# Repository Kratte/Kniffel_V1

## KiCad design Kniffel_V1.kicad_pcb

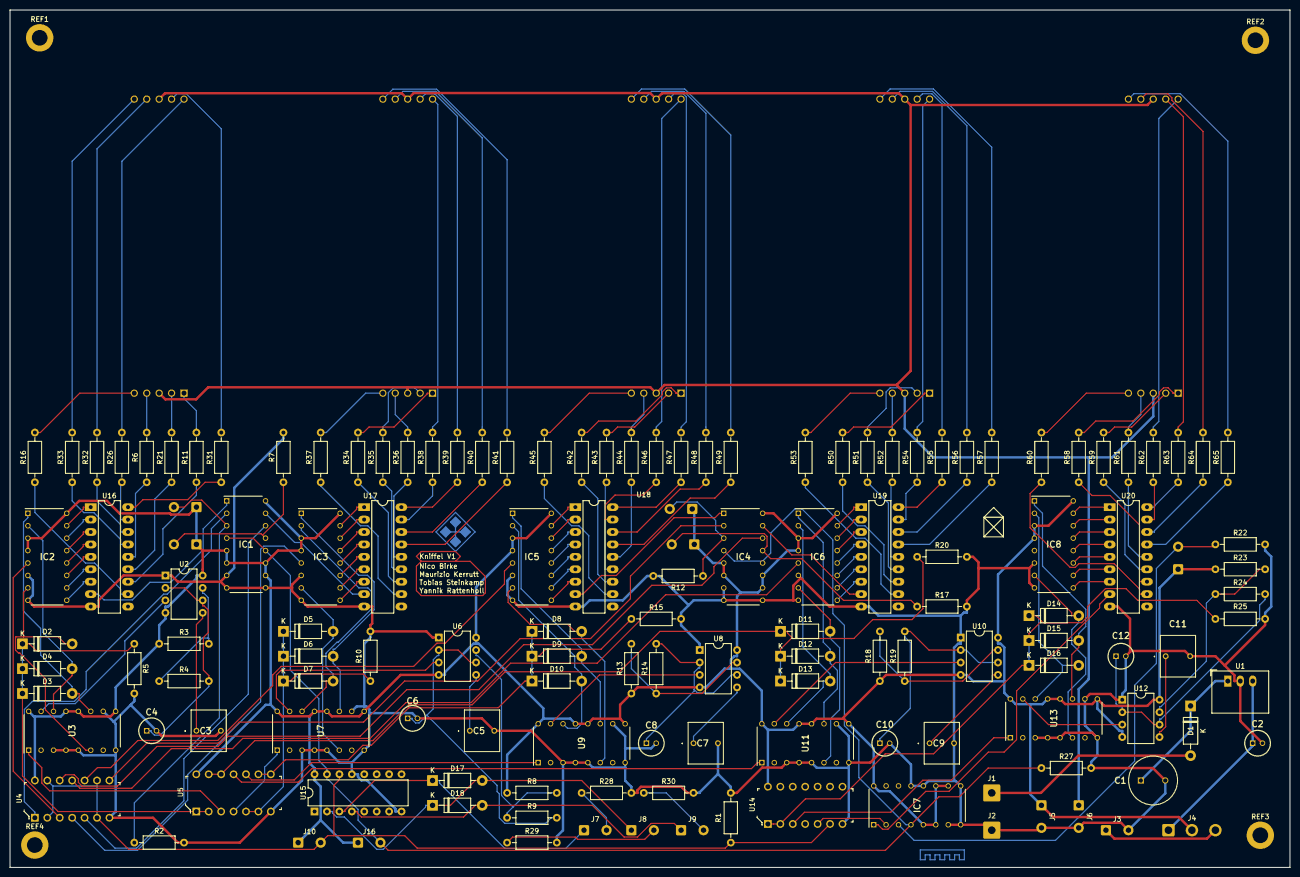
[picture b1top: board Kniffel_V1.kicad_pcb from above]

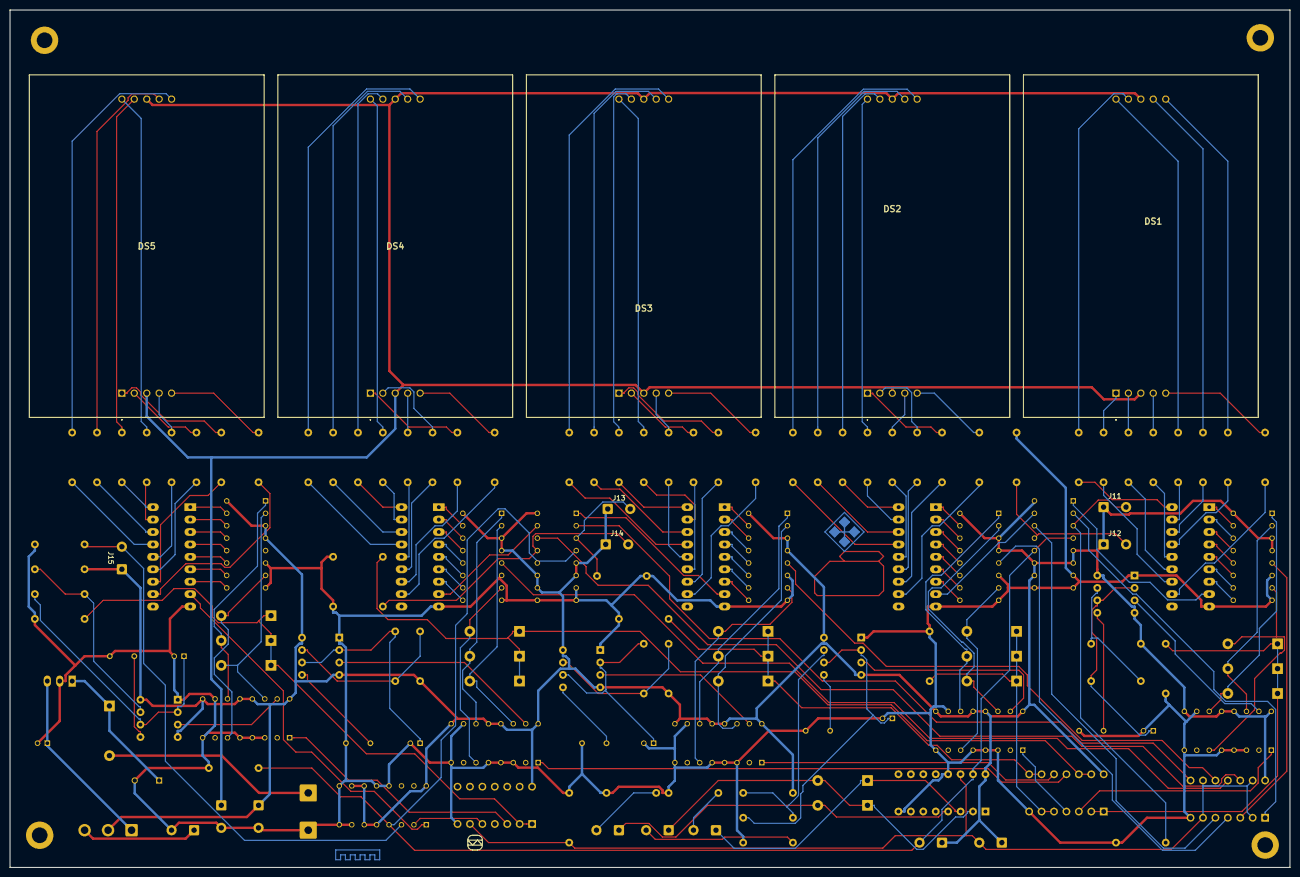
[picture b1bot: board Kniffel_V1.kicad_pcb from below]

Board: 2 copper layers, 261.6 x 175.3 mm, 148 parts (10 on the bottom side), 194 nets.

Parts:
C1: ECA-1HHG331; CAPPRD500W65D1000H1700
C2: ECA-1CM101; CAPPRD200W55D525H1200
C3, C5, C7, C9, C11: FKP2J021001L00HSSD
C4, C6, C8, C10, C12: ECA1HM4R7I; CAPPRD200W55D525H1200
D1: 1N4007; D_DO-41_SOD81_P10.16mm_Horizontal
D2, D3, D4, D5, D6, D7, D8, D9, D10, D11, D12, D13, D14, D15, D16, D17, D18: 1N5817; D_DO-41_SOD81_P10.16mm_Horizontal
DS1, DS2, DS3, DS4, DS5: SA23-12SRWA; SC2312SRWA
IC1, IC4, IC7: CD4027BE; DIP794W53P254L1930H508Q16N
IC2, IC3, IC5, IC6, IC8: CD4511BE; DIP794W53P254L1930H508Q16N
J1: +9V; SolderWire-0.75sqmm_1x01_D1.25mm_OD3.5mm
J2: GND; SolderWire-0.75sqmm_1x01_D1.25mm_OD3.5mm
J3: USB 5V; SolderWire-0.5sqmm_1x02_P4.6mm_D0.9mm_OD2.1mm
J4: Switch; SolderWire-0.75sqmm_1x03_P4.8mm_D1.25mm_OD2.3mm
J5: 5VOUT; SolderWire-0.5sqmm_1x02_P4.6mm_D0.9mm_OD2.1mm
J6: 10VIN; SolderWire-0.5sqmm_1x02_P4.6mm_D0.9mm_OD2.1mm
J7: LED1; SolderWire-0.5sqmm_1x02_P4.6mm_D0.9mm_OD2.1mm
J8: LED2; SolderWire-0.5sqmm_1x02_P4.6mm_D0.9mm_OD2.1mm
J9: LED3; SolderWire-0.5sqmm_1x02_P4.6mm_D0.9mm_OD2.1mm
J10: ROLL_DICE; SolderWire-0.5sqmm_1x02_P4.6mm_D0.9mm_OD2.1mm
J11: DICE1; SolderWire-0.5sqmm_1x02_P4.6mm_D0.9mm_OD2.1mm
J12: DICE2; SolderWire-0.5sqmm_1x02_P4.6mm_D0.9mm_OD2.1mm
J13: DICE3; SolderWire-0.5sqmm_1x02_P4.6mm_D0.9mm_OD2.1mm
J14: DICE4; SolderWire-0.5sqmm_1x02_P4.6mm_D0.9mm_OD2.1mm
J15: DICE5; SolderWire-0.5sqmm_1x02_P4.6mm_D0.9mm_OD2.1mm
J16: RESET; SolderWire-0.5sqmm_1x02_P4.6mm_D0.9mm_OD2.1mm
R1, R27: R3K3; R_Axial_DIN0207_L6.3mm_D2.5mm_P10.16mm_Horizontal
R2, R3, R4, R5, R7, R8, R9, R10, R12, R13, R14, R15, R17, R18, R19, R20, R22, R23, R24, R25: 3K3R; R_Axial_DIN0207_L6.3mm_D2.5mm_P10.16mm_Horizontal
R6, R11, R21, R26, R31, R32, R33, R34, R35, R36, R38, R39, R40, R41, R42, R43, R44, R46, R47, R48, R49, R50, R51, R52, R54, R55, R56, R57, R58, R59, R61, R62, R63, R64, R65: 120R; R_Axial_DIN0207_L6.3mm_D2.5mm_P10.16mm_Horizontal
R16, R37, R45, R53, R60: 270R; R_Axial_DIN0207_L6.3mm_D2.5mm_P10.16mm_Horizontal
R28, R29, R30: 180R; R_Axial_DIN0207_L6.3mm_D2.5mm_P10.16mm_Horizontal
REF1, REF2, REF3, REF4: MountingHole_3.2mm_M3_DIN965_Pad
U1: R-78HB5.0-0.5; Converter_DCDC_RECOM_R-78HB-0.5_THT
U2, U6, U8, U10, U12: NE555P; DIP-8_W7.62mm
U3, U7, U9, U11, U13: CD4029BE; DIP794W53P254L1930H508Q16N
U4, U5, U14: CD4093BE; DIP-14_W3mm
U15: 4017; DIP-16_W7.62mm
U16, U17, U18, U19, U20: ULN2803A; DIP-18_W7.62mm_LongPads

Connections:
+5V: IC1.5 (K2), IC1.6 (J2), IC1.10 (J1), IC1.11 (K1), IC1.16 (VDD), IC2.3 (~LT), IC2.4 (~BL), IC2.16 (VDD), IC3.3 (~LT), IC3.4 (~BL), IC3.16 (VDD), IC4.5 (K2), IC4.6 (J2), IC4.10 (J1), IC4.11 (K1), IC4.16 (VDD), IC5.3 (~LT), IC5.4 (~BL), IC5.16 (VDD), IC6.3 (~LT), IC6.4 (~BL), IC6.16 (VDD), IC7.5 (K2), IC7.6 (J2), IC7.10 (J1), IC7.11 (K1), IC7.16 (VDD), IC8.3 (~LT), IC8.4 (~BL), IC8.16 (VDD), J4.2, J5.1, J10.1, J11.1, J12.1, J13.1, J14.1, J15.1, J16.1, R3.1, R8.1, R13.1, R18.1, R23.1, U2.4 (R), U2.8 (VCC), U3.9 (B/D), U3.12 (J2), U3.13 (J3), U3.16 (VDD), U4.14 (VDD), U5.14 (VDD), U6.4 (R), U6.8 (VCC), U7.9 (B/D), U7.12 (J2), U7.13 (J3), U7.16 (VDD), U8.4 (R), U8.8 (VCC), U9.9 (B/D), U9.12 (J2), U9.13 (J3), U9.16 (VDD), U10.4 (R), U10.8 (VCC), U11.9 (B/D), U11.12 (J2), U11.13 (J3), U11.16 (VDD), U12.4 (R), U12.8 (VCC), U13.9 (B/D), U13.12 (J2), U13.13 (J3), U13.16 (VDD), U14.14 (VDD), U15.16 (VDD)
+10V: DS1.3 (COM_A_1), DS1.8 (COM_A_2), DS2.3 (COM_A_1), DS2.8 (COM_A_2), DS3.3 (COM_A_1), DS3.8 (COM_A_2), DS4.3 (COM_A_1), DS4.8 (COM_A_2), DS5.3 (COM_A_1), DS5.8 (COM_A_2), J6.1
/Dice1/D2: D5.1 (K), D6.1 (K), D7.1 (K), R10.1, U5.5 (C), U5.6 (D)
/Dice1/D2Hold: IC1.14 (~Q1), U4.5 (C)
/Dice1/D2Latch: IC3.5 (LE/~STROBE), U4.4 (K)
/Dice1/D2Q: IC1.15 (Q1), U17.8 (I8)
/Dice1/D2R: U5.4 (K), U7.1 (PE)
/Dice1/D2Set: IC1.13 (CLOCK1), J12.2, R7.1
/Dice1/D3: D8.1 (K), D9.1 (K), D10.1 (K), R15.1, U5.8 (E), U5.9 (F)
/Dice1/D3Hold: IC4.2 (~Q2), U4.8 (E)
/Dice1/D3Latch: IC5.5 (LE/~STROBE), U4.10 (L)
/Dice1/D3R: U5.10 (L), U9.1 (PE)
/Dice1/D4: D11.1 (K), D12.1 (K), D13.1 (K), R20.1, U5.12 (G), U5.13 (H)
/Dice1/D4Hold: IC4.14 (~Q1), U4.12 (G)
/Dice1/D4Latch: IC6.5 (LE/~STROBE), U4.11 (M)
/Dice1/D4R: U5.11 (M), U11.1 (PE)
/Dice1/Roll: J10.2, R1.1, U4.2 (B), U4.6 (D), U4.9 (F), U4.13 (H), U14.6 (D), U15.14 (CLK)
/Dice3/D4Q: IC4.15 (Q1), U19.8 (I8)
/Dice3/D4Set: IC4.13 (CLOCK1), J14.2, R17.1
D5Hold: IC7.2 (~Q2), U14.5 (C)
GND: C1.2, C2.2, C3.2, C4.2, C5.2, C6.2, C7.2, C8.2, C9.2, C10.2, C11.2, C12.2, IC1.7 (SET2), IC1.8 (VSS), IC1.9 (SET1), IC2.6 (D_1), IC2.8 (VSS), IC3.6 (D_1), IC3.8 (VSS), IC4.7 (SET2), IC4.8 (VSS), IC4.9 (SET1), IC5.6 (D_1), IC5.8 (VSS), IC6.6 (D_1), IC6.8 (VSS), IC7.7 (SET2), IC7.8 (VSS), IC7.9 (SET1), IC7.12 (RESET1), IC7.13 (CLOCK1), IC8.6 (D_1), IC8.8 (VSS), J2.1, J3.2, J5.2, J6.2, R1.2, R2.2, R5.2, R7.2, R10.2, R12.2, R15.2, R17.2, R20.2, R22.2, R25.2, R27.2, R28.2, R29.2, R30.2, U1.2 (GND), U2.1 (GND), U3.3 (J4), U3.4 (J1), U3.5 (Cin), U3.8 (VSS), U3.10 (U/D), U4.7 (VCC), U5.7 (VCC), U6.1 (GND), U7.3 (J4), U7.4 (J1), U7.5 (Cin), U7.8 (VSS), U7.10 (U/D), U8.1 (GND), U9.3 (J4), U9.4 (J1), U9.5 (Cin), U9.8 (VSS), U9.10 (U/D), U10.1 (GND), U11.3 (J4), U11.4 (J1), U11.5 (Cin), U11.8 (VSS), U11.10 (U/D), U12.1 (GND), U13.3 (J4), U13.4 (J1), U13.5 (Cin), U13.8 (VSS), U13.10 (U/D), U14.7 (VCC), U15.8 (VSS), U15.13 (CKEN), U16.9 (GND), U17.9 (GND), U18.9 (GND), U19.9 (GND), U20.9 (GND)
unnamed: C1.1, D1.1 (K), U1.1 (IN)
unnamed: C2.1, J4.1, U1.3 (OUT)
unnamed: C3.1, U2.5 (CV)
unnamed: C4.1, R4.2, U2.2 (TR), U2.6 (THR)
unnamed: C5.1, U6.5 (CV)
unnamed: C6.1, R9.2, U6.2 (TR), U6.6 (THR)
unnamed: C7.1, U8.5 (CV)
unnamed: C8.1, R14.2, U8.2 (TR), U8.6 (THR)
unnamed: C9.1, U10.5 (CV)
unnamed: C10.1, R19.2, U10.2 (TR), U10.6 (THR)
unnamed: C11.1, U12.5 (CV)
unnamed: C12.1, R24.2, U12.2 (TR), U12.6 (THR)
unnamed: D1.2 (A), J1.1
unnamed: D2.1 (K), D3.1 (K), D4.1 (K), R5.1, U5.1 (A), U5.2 (B)
unnamed: D2.2 (A), IC2.7 (A_1), U3.6 (Q1)
unnamed: D3.2 (A), IC2.1 (B_1), U3.11 (Q2)
unnamed: D4.2 (A), IC2.2 (C_1), U3.14 (Q3)
unnamed: D5.2 (A), IC3.7 (A_1), U7.6 (Q1)
unnamed: D6.2 (A), IC3.1 (B_1), U7.11 (Q2)
unnamed: D7.2 (A), IC3.2 (C_1), U7.14 (Q3)
unnamed: D8.2 (A), IC5.7 (A_1), U9.6 (Q1)
unnamed: D9.2 (A), IC5.1 (B_1), U9.11 (Q2)
unnamed: D10.2 (A), IC5.2 (C_1), U9.14 (Q3)
unnamed: D11.2 (A), IC6.7 (A_1), U11.6 (Q1)
unnamed: D12.2 (A), IC6.1 (B_1), U11.11 (Q2)
unnamed: D13.2 (A), IC6.2 (C_1), U11.14 (Q3)
unnamed: D14.1 (K), D15.1 (K), D16.1 (K), R25.1, U14.1 (A), U14.2 (B)
unnamed: D14.2 (A), IC8.7 (A_1), U13.6 (Q1)
unnamed: D15.2 (A), IC8.1 (B_1), U13.11 (Q2)
unnamed: D16.2 (A), IC8.2 (C_1), U13.14 (Q3)
unnamed: D17.1 (K), J7.1, U15.3 (Q0)
unnamed: D17.2 (A), D18.1 (K), J8.1, U15.2 (Q1)
unnamed: D18.2 (A), J9.1, U15.4 (Q2)
unnamed: DS1.1 (K_E), R11.2
unnamed: DS1.2 (K_D), R21.2
unnamed: DS1.4 (K_C), R6.2
unnamed: DS1.5 (K_DP), R16.2
unnamed: DS1.6 (K_B), R33.2
unnamed: DS1.7 (K_A), R32.2
unnamed: DS1.9 (K_F), R31.2
unnamed: DS1.10 (K_G), R26.2
unnamed: DS2.1 (K_E), R34.2
unnamed: DS2.2 (K_D), R35.2
unnamed: DS2.4 (K_C), R36.2
unnamed: DS2.5 (K_DP), R37.2
unnamed: DS2.6 (K_B), R41.2
unnamed: DS2.7 (K_A), R40.2
unnamed: DS2.9 (K_F), R39.2
unnamed: DS2.10 (K_G), R38.2
unnamed: DS3.1 (K_E), R42.2
unnamed: DS3.2 (K_D), R43.2
unnamed: DS3.4 (K_C), R44.2
unnamed: DS3.5 (K_DP), R45.2
unnamed: DS3.6 (K_B), R49.2
unnamed: DS3.7 (K_A), R48.2
unnamed: DS3.9 (K_F), R47.2
unnamed: DS3.10 (K_G), R46.2
unnamed: DS4.1 (K_E), R50.2
unnamed: DS4.2 (K_D), R51.2
unnamed: DS4.4 (K_C), R52.2
unnamed: DS4.5 (K_DP), R53.2
unnamed: DS4.6 (K_B), R57.2
unnamed: DS4.7 (K_A), R56.2
unnamed: DS4.9 (K_F), R55.2
unnamed: DS4.10 (K_G), R54.2
unnamed: DS5.1 (K_E), R58.2
unnamed: DS5.2 (K_D), R59.2
unnamed: DS5.4 (K_C), R61.2
unnamed: DS5.5 (K_DP), R60.2
unnamed: DS5.6 (K_B), R65.2
unnamed: DS5.7 (K_A), R64.2
unnamed: DS5.9 (K_F), R63.2
unnamed: DS5.10 (K_G), R62.2
unnamed: IC1.1 (Q2), U16.8 (I8)
unnamed: IC1.2 (~Q2), U4.1 (A)
unnamed: IC1.3 (CLOCK2), J11.2, R2.1
unnamed: IC2.5 (LE/~STROBE), U4.3 (J)
unnamed: IC2.9 (E), U16.7 (I7)
unnamed: IC2.10 (D_2), U16.6 (I6)
unnamed: IC2.11 (C_2), U16.5 (I5)
unnamed: IC2.12 (B_2), U16.4 (I4)
unnamed: IC2.13 (A_2), U16.3 (I3)
unnamed: IC2.14 (G), U16.2 (I2)
unnamed: IC2.15 (F), U16.1 (I1)
unnamed: IC3.9 (E), U17.7 (I7)
unnamed: IC3.10 (D_2), U17.6 (I6)
unnamed: IC3.11 (C_2), U17.5 (I5)
unnamed: IC3.12 (B_2), U17.4 (I4)
unnamed: IC3.13 (A_2), U17.3 (I3)
unnamed: IC3.14 (G), U17.2 (I2)
unnamed: IC3.15 (F), U17.1 (I1)
unnamed: IC4.1 (Q2), U18.8 (I8)
unnamed: IC4.3 (CLOCK2), J13.2, R12.1
unnamed: IC5.9 (E), U18.7 (I7)
unnamed: IC5.10 (D_2), U18.6 (I6)
unnamed: IC5.11 (C_2), U18.5 (I5)
unnamed: IC5.12 (B_2), U18.4 (I4)
unnamed: IC5.13 (A_2), U18.3 (I3)
unnamed: IC5.14 (G), U18.2 (I2)
unnamed: IC5.15 (F), U18.1 (I1)
unnamed: IC6.9 (E), U19.7 (I7)
unnamed: IC6.10 (D_2), U19.6 (I6)
unnamed: IC6.11 (C_2), U19.5 (I5)
unnamed: IC6.12 (B_2), U19.4 (I4)
unnamed: IC6.13 (A_2), U19.3 (I3)
unnamed: IC6.14 (G), U19.2 (I2)
unnamed: IC6.15 (F), U19.1 (I1)
unnamed: IC7.1 (Q2), U20.8 (I8)
unnamed: IC7.3 (CLOCK2), J15.2, R22.1
unnamed: IC8.9 (E), U20.7 (I7)
unnamed: IC8.10 (D_2), U20.6 (I6)
unnamed: IC8.11 (C_2), U20.5 (I5)
unnamed: IC8.12 (B_2), U20.4 (I4)
unnamed: IC8.13 (A_2), U20.3 (I3)
unnamed: IC8.14 (G), U20.2 (I2)
unnamed: IC8.15 (F), U20.1 (I1)
unnamed: J3.1, J4.3
unnamed: J7.2, R28.1
unnamed: J8.2, R29.1
unnamed: J9.2, R30.1
unnamed: R3.2, R4.1, U2.7 (DIS)
unnamed: R6.1, U16.14 (O5)
unnamed: R8.2, R9.1, U6.7 (DIS)
unnamed: R11.1, U16.12 (O7)
unnamed: R13.2, R14.1, U8.7 (DIS)
unnamed: R16.1, U16.11 (O8)
unnamed: R18.2, R19.1, U10.7 (DIS)
unnamed: R21.1, U16.13 (O6)
unnamed: R23.2, R24.1, U12.7 (DIS)
unnamed: R26.1, U16.17 (O2)
unnamed: R31.1, U16.18 (O1)
unnamed: R32.1, U16.16 (O3)
unnamed: R33.1, U16.15 (O4)
unnamed: R34.1, U17.12 (O7)
unnamed: R35.1, U17.13 (O6)
unnamed: R36.1, U17.14 (O5)
unnamed: R37.1, U17.11 (O8)
unnamed: R38.1, U17.17 (O2)
unnamed: R39.1, U17.18 (O1)
unnamed: R40.1, U17.16 (O3)
unnamed: R41.1, U17.15 (O4)
unnamed: R42.1, U18.12 (O7)
unnamed: R43.1, U18.13 (O6)
unnamed: R44.1, U18.14 (O5)
unnamed: R45.1, U18.11 (O8)
unnamed: R46.1, U18.17 (O2)
unnamed: R47.1, U18.18 (O1)
unnamed: R48.1, U18.16 (O3)
unnamed: R49.1, U18.15 (O4)
unnamed: R50.1, U19.12 (O7)
unnamed: R51.1, U19.13 (O6)
unnamed: R52.1, U19.14 (O5)
unnamed: R53.1, U19.11 (O8)
unnamed: R54.1, U19.17 (O2)
unnamed: R55.1, U19.18 (O1)
unnamed: R56.1, U19.16 (O3)
unnamed: R57.1, U19.15 (O4)
unnamed: R58.1, U20.12 (O7)
unnamed: R59.1, U20.13 (O6)
unnamed: R60.1, U20.11 (O8)
unnamed: R61.1, U20.14 (O5)
unnamed: R62.1, U20.17 (O2)
unnamed: R63.1, U20.18 (O1)
unnamed: R64.1, U20.16 (O3)
unnamed: R65.1, U20.15 (O4)
unnamed: U2.3 (Q), U3.15 (CK)
unnamed: U3.1 (PE), U5.3 (J)
unnamed: U6.3 (Q), U7.15 (CK)
unnamed: U8.3 (Q), U9.15 (CK)
unnamed: U10.3 (Q), U11.15 (CK)
unnamed: U12.3 (Q), U13.15 (CK)
unnamed: U13.1 (PE), U14.3 (J)
Reset: IC1.4 (RESET2), IC1.12 (RESET1), IC4.4 (RESET2), IC4.12 (RESET1), IC7.4 (RESET2), J16.2, R27.1, U15.15 (Reset)

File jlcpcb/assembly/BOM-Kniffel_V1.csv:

Comment,Designator,Footprint,LCSC
+9V,J1,SolderWire-0.75sqmm_1x01_D1.25mm_OD3.5mm,
3K3R,R18,R_Axial_DIN0207_L6.3mm_D2.5mm_P10.16mm_Horizontal,
CD4511BE,IC3,DIP794W53P254L1930H508Q16N,
3K3R,R10,R_Axial_DIN0207_L6.3mm_D2.5mm_P10.16mm_Horizontal,
3K3R,R25,R_Axial_DIN0207_L6.3mm_D2.5mm_P10.16mm_Horizontal,
3K3R,R4,R_Axial_DIN0207_L6.3mm_D2.5mm_P10.16mm_Horizontal,
3K3R,R15,R_Axial_DIN0207_L6.3mm_D2.5mm_P10.16mm_Horizontal,
3K3R,R20,R_Axial_DIN0207_L6.3mm_D2.5mm_P10.16mm_Horizontal,
3K3R,R3,R_Axial_DIN0207_L6.3mm_D2.5mm_P10.16mm_Horizontal,
CD4511BE,IC5,DIP794W53P254L1930H508Q16N,
NE555P,U6,DIP-8_W7.62mm,
FKP2J021001L00HSSD,C3,FKP2J021001L00HSSD,
3K3R,R2,R_Axial_DIN0207_L6.3mm_D2.5mm_P10.16mm_Horizontal,
1N5817,D11,D_DO-41_SOD81_P10.16mm_Horizontal,
CD4511BE,IC8,DIP794W53P254L1930H508Q16N,
1N4007,D1,D_DO-41_SOD81_P10.16mm_Horizontal,
CD4511BE,IC2,DIP794W53P254L1930H508Q16N,
1N5817,D3,D_DO-41_SOD81_P10.16mm_Horizontal,
NE555P,U10,DIP-8_W7.62mm,
Switch,J4,SolderWire-0.75sqmm_1x03_P4.8mm_D1.25mm_OD2.3mm,
FKP2J021001L00HSSD,C11,FKP2J021001L00HSSD,
1N5817,D10,D_DO-41_SOD81_P10.16mm_Horizontal,
CD4029BE,U7,DIP794W53P254L1930H508Q16N,
1N5817,D7,D_DO-41_SOD81_P10.16mm_Horizontal,
CD4027BE,IC4,DIP794W53P254L1930H508Q16N,
270R,R16,R_Axial_DIN0207_L6.3mm_D2.5mm_P10.16mm_Horizontal,
1N5817,D16,D_DO-41_SOD81_P10.16mm_Horizontal,
GND,J2,SolderWire-0.75sqmm_1x01_D1.25mm_OD3.5mm,
ECA-1CM101,C2,CAPPRD200W55D525H1200,
ECA1HM4R7I,C4,CAPPRD200W55D525H1200,
CD4093BE,U4,DIP-14_W3mm,
1N5817,D8,D_DO-41_SOD81_P10.16mm_Horizontal,
3K3R,R9,R_Axial_DIN0207_L6.3mm_D2.5mm_P10.16mm_Horizontal,
1N5817,D6,D_DO-41_SOD81_P10.16mm_Horizontal,
3K3R,R22,R_Axial_DIN0207_L6.3mm_D2.5mm_P10.16mm_Horizontal,
1N5817,D13,D_DO-41_SOD81_P10.16mm_Horizontal,
NE555P,U2,DIP-8_W7.62mm,
1N5817,D4,D_DO-41_SOD81_P10.16mm_Horizontal,
CD4029BE,U3,DIP794W53P254L1930H508Q16N,
3K3R,R8,R_Axial_DIN0207_L6.3mm_D2.5mm_P10.16mm_Horizontal,
ECA1HM4R7I,C10,CAPPRD200W55D525H1200,
120R,R26,R_Axial_DIN0207_L6.3mm_D2.5mm_P10.16mm_Horizontal,
ECA1HM4R7I,C12,CAPPRD200W55D525H1200,
3K3R,R12,R_Axial_DIN0207_L6.3mm_D2.5mm_P10.16mm_Horizontal,
3K3R,R7,R_Axial_DIN0207_L6.3mm_D2.5mm_P10.16mm_Horizontal,
R3K3,R1,R_Axial_DIN0207_L6.3mm_D2.5mm_P10.16mm_Horizontal,
CD4029BE,U11,DIP794W53P254L1930H508Q16N,
CD4027BE,IC7,DIP794W53P254L1930H508Q16N,
R-78HB5.0-0.5,U1,Converter_DCDC_RECOM_R-78HB-0.5_THT,
1N5817,D15,D_DO-41_SOD81_P10.16mm_Horizontal,
USB 5V,J3,SolderWire-0.5sqmm_1x02_P4.6mm_D0.9mm_OD2.1mm,
CD4511BE,IC6,DIP794W53P254L1930H508Q16N,
NE555P,U12,DIP-8_W7.62mm,
CD4093BE,U5,DIP-14_W3mm,
FKP2J021001L00HSSD,C5,FKP2J021001L00HSSD,
1N5817,D2,D_DO-41_SOD81_P10.16mm_Horizontal,
3K3R,R5,R_Axial_DIN0207_L6.3mm_D2.5mm_P10.16mm_Horizontal,
FKP2J021001L00HSSD,C7,FKP2J021001L00HSSD,
3K3R,R24,R_Axial_DIN0207_L6.3mm_D2.5mm_P10.16mm_Horizontal,
ECA1HM4R7I,C8,CAPPRD200W55D525H1200,
1N5817,D14,D_DO-41_SOD81_P10.16mm_Horizontal,
CD4093BE,U14,DIP-14_W3mm,
CD4027BE,IC1,DIP794W53P254L1930H508Q16N,
3K3R,R23,R_Axial_DIN0207_L6.3mm_D2.5mm_P10.16mm_Horizontal,
ECA1HM4R7I,C6,CAPPRD200W55D525H1200,
1N5817,D5,D_DO-41_SOD81_P10.16mm_Horizontal,
120R,R6,R_Axial_DIN0207_L6.3mm_D2.5mm_P10.16mm_Horizontal,
3K3R,R17,R_Axial_DIN0207_L6.3mm_D2.5mm_P10.16mm_Horizontal,
120R,R21,R_Axial_DIN0207_L6.3mm_D2.5mm_P10.16mm_Horizontal,
1N5817,D12,D_DO-41_SOD81_P10.16mm_Horizontal,
ECA-1HHG331,C1,CAPPRD500W65D1000H1700,
120R,R11,R_Axial_DIN0207_L6.3mm_D2.5mm_P10.16mm_Horizontal,
FKP2J021001L00HSSD,C9,FKP2J021001L00HSSD,
3K3R,R13,R_Axial_DIN0207_L6.3mm_D2.5mm_P10.16mm_Horizontal,
3K3R,R19,R_Axial_DIN0207_L6.3mm_D2.5mm_P10.16mm_Horizontal,
3K3R,R14,R_Axial_DIN0207_L6.3mm_D2.5mm_P10.16mm_Horizontal,
1N5817,D9,D_DO-41_SOD81_P10.16mm_Horizontal,
CD4029BE,U13,DIP794W53P254L1930H508Q16N,
CD4029BE,U9,DIP794W53P254L1930H508Q16N,
NE555P,U8,DIP-8_W7.62mm,
SA23-12SRWA,DS1,SC2312SRWA,
SA23-12SRWA,DS2,SC2312SRWA,
SA23-12SRWA,DS4,SC2312SRWA,
SA23-12SRWA,DS5,SC2312SRWA,
SA23-12SRWA,DS3,SC2312SRWA,
120R,R50,R_Axial_DIN0207_L6.3mm_D2.5mm_P10.16mm_Horizontal,
120R,R47,R_Axial_DIN0207_L6.3mm_D2.5mm_P10.16mm_Horizontal,
270R,R37,R_Axial_DIN0207_L6.3mm_D2.5mm_P10.16mm_Horizontal,
120R,R35,R_Axial_DIN0207_L6.3mm_D2.5mm_P10.16mm_Horizontal,
10VIN,J6,SolderWire-0.5sqmm_1x02_P4.6mm_D0.9mm_OD2.1mm,
ULN2803A,U17,DIP-18_W7.62mm_LongPads,
5VOUT,J5,SolderWire-0.5sqmm_1x02_P4.6mm_D0.9mm_OD2.1mm,
180R,R28,R_Axial_DIN0207_L6.3mm_D2.5mm_P10.16mm_Horizontal,
120R,R42,R_Axial_DIN0207_L6.3mm_D2.5mm_P10.16mm_Horizontal,
270R,R60,R_Axial_DIN0207_L6.3mm_D2.5mm_P10.16mm_Horizontal,
1N5817,D18,D_DO-41_SOD81_P10.16mm_Horizontal,
120R,R54,R_Axial_DIN0207_L6.3mm_D2.5mm_P10.16mm_Horizontal,
LED1,J7,SolderWire-0.5sqmm_1x02_P4.6mm_D0.9mm_OD2.1mm,
DICE1,J11,SolderWire-0.5sqmm_1x02_P4.6mm_D0.9mm_OD2.1mm,
120R,R34,R_Axial_DIN0207_L6.3mm_D2.5mm_P10.16mm_Horizontal,
ROLL_DICE,J10,SolderWire-0.5sqmm_1x02_P4.6mm_D0.9mm_OD2.1mm,
ULN2803A,U19,DIP-18_W7.62mm_LongPads,
120R,R41,R_Axial_DIN0207_L6.3mm_D2.5mm_P10.16mm_Horizontal,
120R,R38,R_Axial_DIN0207_L6.3mm_D2.5mm_P10.16mm_Horizontal,
270R,R45,R_Axial_DIN0207_L6.3mm_D2.5mm_P10.16mm_Horizontal,
120R,R40,R_Axial_DIN0207_L6.3mm_D2.5mm_P10.16mm_Horizontal,
120R,R63,R_Axial_DIN0207_L6.3mm_D2.5mm_P10.16mm_Horizontal,
120R,R51,R_Axial_DIN0207_L6.3mm_D2.5mm_P10.16mm_Horizontal,
120R,R62,R_Axial_DIN0207_L6.3mm_D2.5mm_P10.16mm_Horizontal,
120R,R58,R_Axial_DIN0207_L6.3mm_D2.5mm_P10.16mm_Horizontal,
ULN2803A,U20,DIP-18_W7.62mm_LongPads,
120R,R65,R_Axial_DIN0207_L6.3mm_D2.5mm_P10.16mm_Horizontal,
120R,R56,R_Axial_DIN0207_L6.3mm_D2.5mm_P10.16mm_Horizontal,
120R,R55,R_Axial_DIN0207_L6.3mm_D2.5mm_P10.16mm_Horizontal,
180R,R30,R_Axial_DIN0207_L6.3mm_D2.5mm_P10.16mm_Horizontal,
120R,R59,R_Axial_DIN0207_L6.3mm_D2.5mm_P10.16mm_Horizontal,
4017,U15,DIP-16_W7.62mm,
R3K3,R27,R_Axial_DIN0207_L6.3mm_D2.5mm_P10.16mm_Horizontal,
120R,R46,R_Axial_DIN0207_L6.3mm_D2.5mm_P10.16mm_Horizontal,
120R,R31,R_Axial_DIN0207_L6.3mm_D2.5mm_P10.16mm_Horizontal,
120R,R49,R_Axial_DIN0207_L6.3mm_D2.5mm_P10.16mm_Horizontal,
DICE4,J14,SolderWire-0.5sqmm_1x02_P4.6mm_D0.9mm_OD2.1mm,
ULN2803A,U18,DIP-18_W7.62mm_LongPads,
120R,R33,R_Axial_DIN0207_L6.3mm_D2.5mm_P10.16mm_Horizontal,
120R,R36,R_Axial_DIN0207_L6.3mm_D2.5mm_P10.16mm_Horizontal,
DICE2,J12,SolderWire-0.5sqmm_1x02_P4.6mm_D0.9mm_OD2.1mm,
DICE5,J15,SolderWire-0.5sqmm_1x02_P4.6mm_D0.9mm_OD2.1mm,
120R,R32,R_Axial_DIN0207_L6.3mm_D2.5mm_P10.16mm_Horizontal,
LED3,J9,SolderWire-0.5sqmm_1x02_P4.6mm_D0.9mm_OD2.1mm,
180R,R29,R_Axial_DIN0207_L6.3mm_D2.5mm_P10.16mm_Horizontal,
120R,R43,R_Axial_DIN0207_L6.3mm_D2.5mm_P10.16mm_Horizontal,
120R,R48,R_Axial_DIN0207_L6.3mm_D2.5mm_P10.16mm_Horizontal,
120R,R64,R_Axial_DIN0207_L6.3mm_D2.5mm_P10.16mm_Horizontal,
120R,R57,R_Axial_DIN0207_L6.3mm_D2.5mm_P10.16mm_Horizontal,
120R,R44,R_Axial_DIN0207_L6.3mm_D2.5mm_P10.16mm_Horizontal,
LED2,J8,SolderWire-0.5sqmm_1x02_P4.6mm_D0.9mm_OD2.1mm,
RESET,J16,SolderWire-0.5sqmm_1x02_P4.6mm_D0.9mm_OD2.1mm,
ULN2803A,U16,DIP-18_W7.62mm_LongPads,
270R,R53,R_Axial_DIN0207_L6.3mm_D2.5mm_P10.16mm_Horizontal,
120R,R61,R_Axial_DIN0207_L6.3mm_D2.5mm_P10.16mm_Horizontal,
DICE3,J13,SolderWire-0.5sqmm_1x02_P4.6mm_D0.9mm_OD2.1mm,
1N5817,D17,D_DO-41_SOD81_P10.16mm_Horizontal,
120R,R52,R_Axial_DIN0207_L6.3mm_D2.5mm_P10.16mm_Horizontal,
120R,R39,R_Axial_DIN0207_L6.3mm_D2.5mm_P10.16mm_Horizontal,

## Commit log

2022-04-28 stuff
2022-04-29 final V1
2022-05-02 spelling :)
